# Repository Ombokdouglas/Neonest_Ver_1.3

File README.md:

# Neonest_Ver_1.3
PCB hardware design

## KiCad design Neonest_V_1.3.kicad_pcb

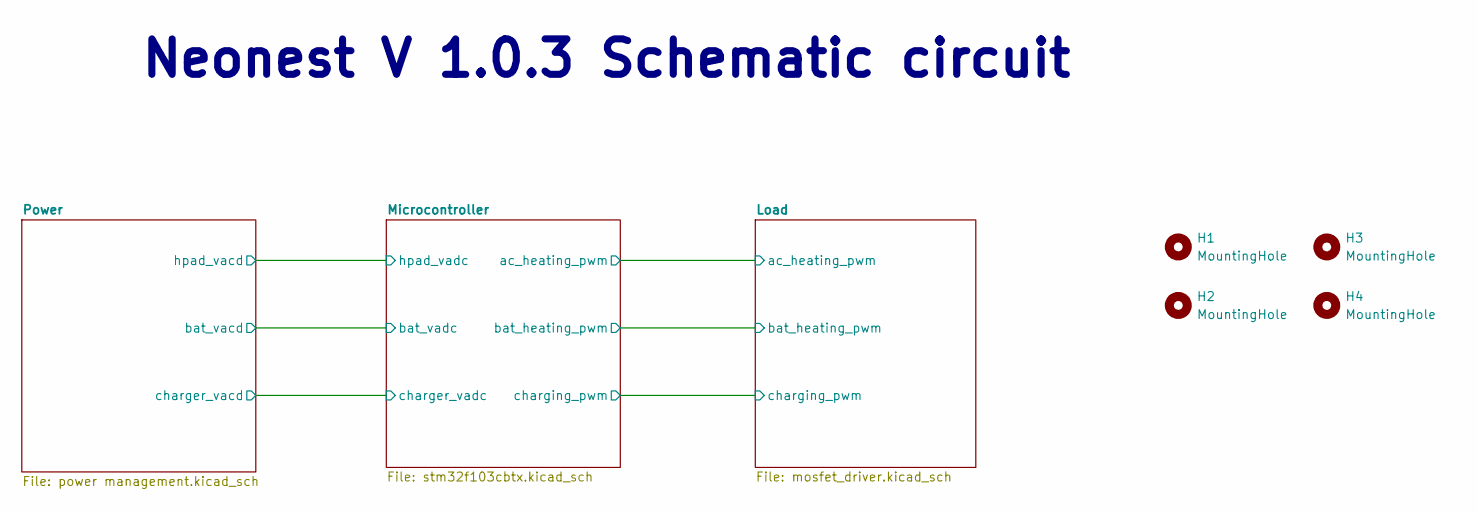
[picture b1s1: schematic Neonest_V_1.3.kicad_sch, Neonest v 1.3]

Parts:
H1, H2, H3, H4: MountingHole; MountingHole_4mm

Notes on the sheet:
Neonest V 1.0.3 Schematic circuit

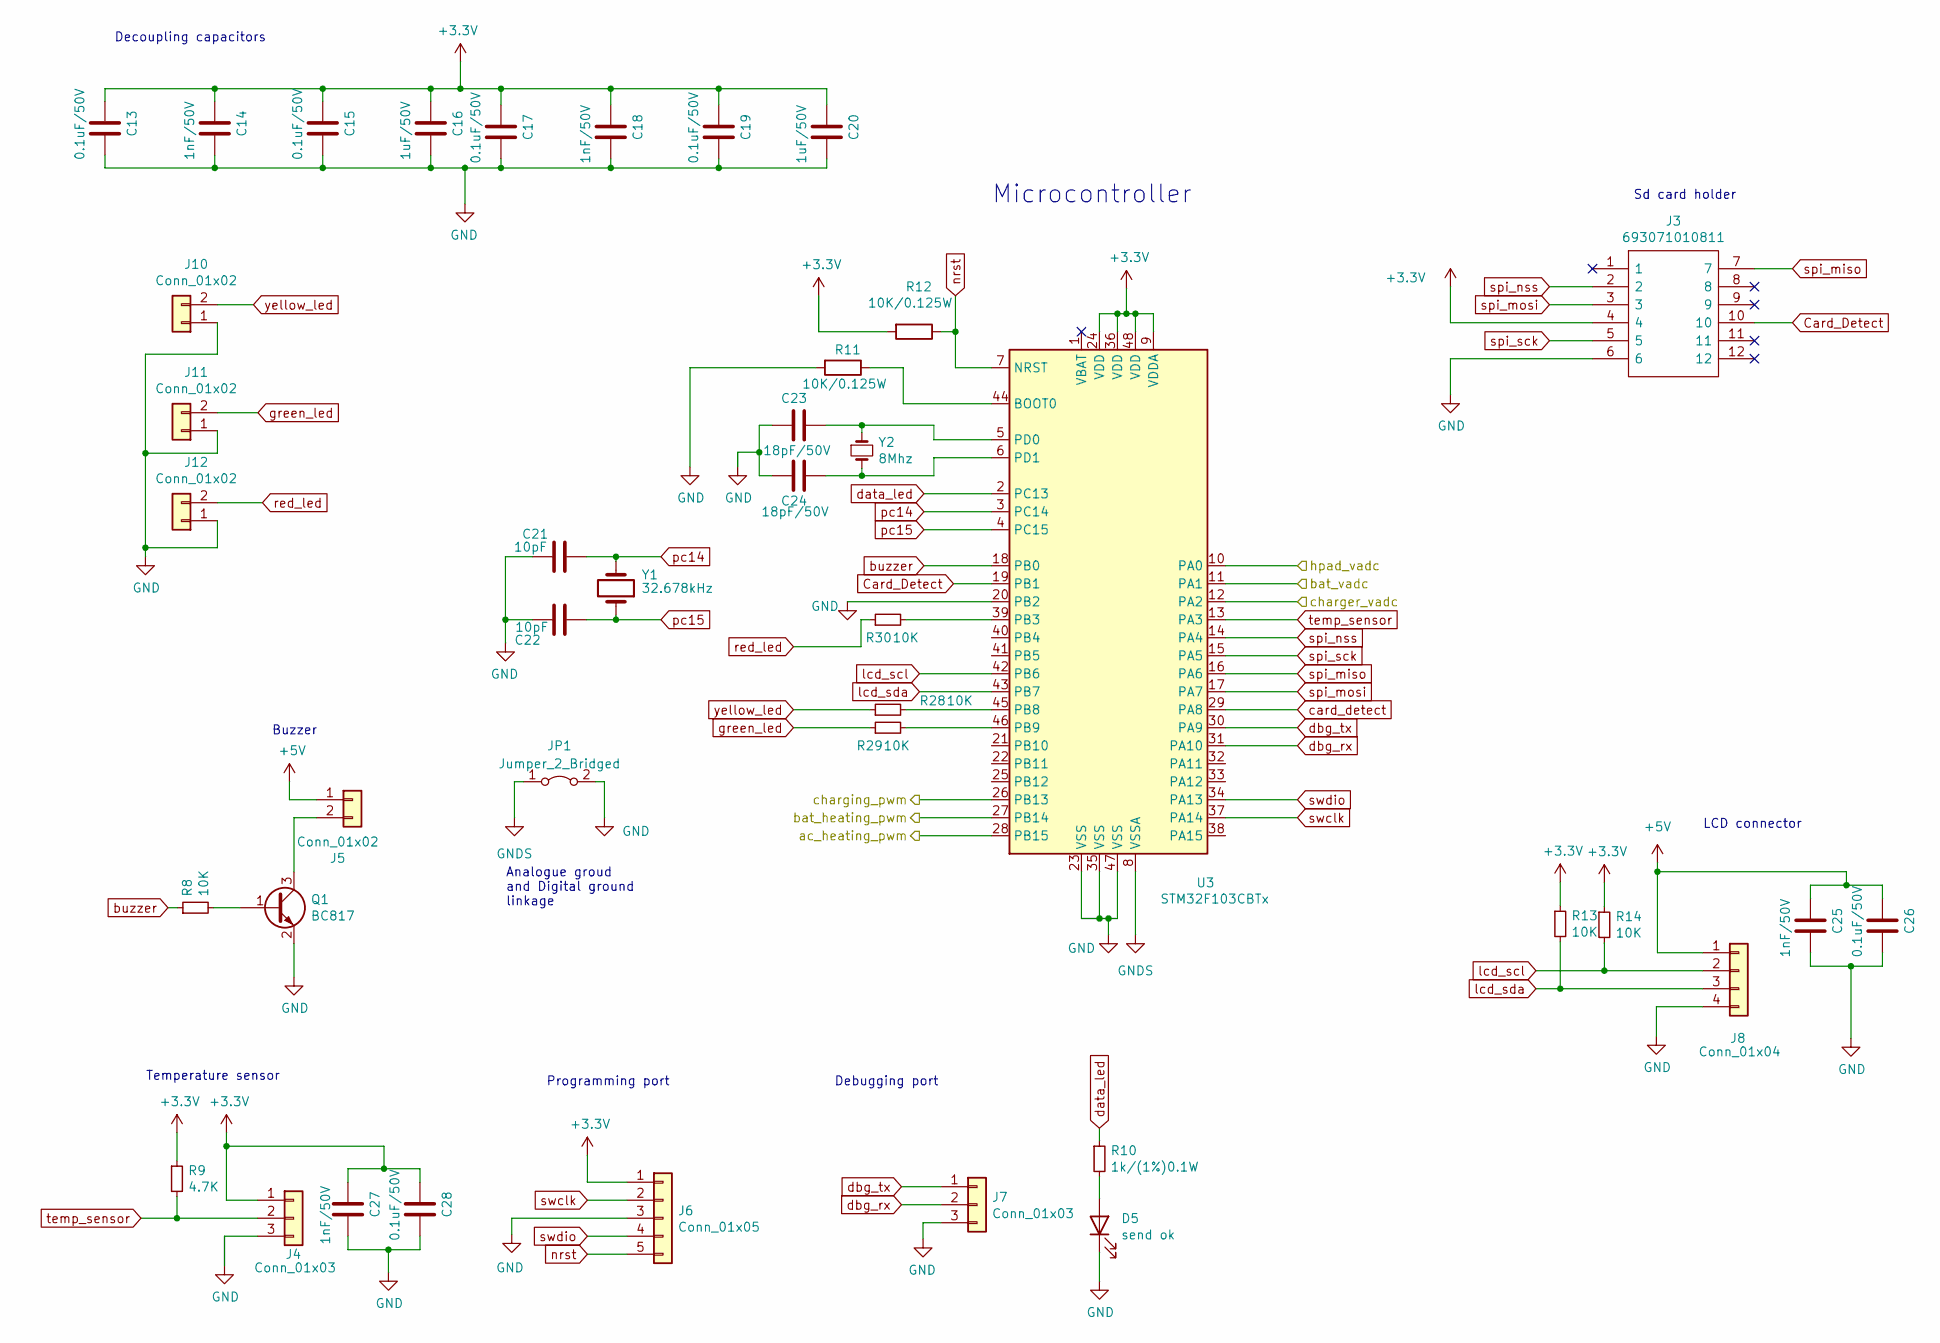
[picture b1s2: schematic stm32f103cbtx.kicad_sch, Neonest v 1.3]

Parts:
C13, C15, C17, C19, C26, C28: 0.1uF/50V; C_0603_1608Metric
C14, C18, C25, C27: 1nF/50V; C_0603_1608Metric
C16, C20: 1uF/50V; C_0603_1608Metric
C21, C22: 10pF; C_0603_1608Metric
C23, C24: 18pF/50V; C_0603_1608Metric
D5: send ok; LED_0603_1608Metric
J3: 693071010811; sd_card; Manufacturer_Part_Number 693071010811; Mouser Part Number 710-693071010811
J4: Conn_01x03; JST_EH_B3B-EH-A_1x03_P2.50mm_Vertical
J5, J10, J11, J12: Conn_01x02; JST_EH_B2B-EH-A_1x02_P2.50mm_Vertical
J6: Conn_01x05; PinHeader_1x05_P2.54mm_Vertical
J7: Conn_01x03; PinHeader_1x03_P2.54mm_Vertical
J8: Conn_01x04; JST_EH_B4B-EH-A_1x04_P2.50mm_Vertical
JP1: Jumper_2_Bridged; SolderJumper-2_P1.3mm_Bridged2Bar_RoundedPad1.0x1.5mm
Q1: BC817; SOT-23
R8, R13, R14, R28, R29, R30: 10K; R_0603_1608Metric
R9: 4.7K; R_0603_1608Metric
R10: 1k/(1%)0.1W; R_0603_1608Metric
R11, R12: 10K/0.125W; R_0603_1608Metric
U3: STM32F103CBTx; LQFP-48_7x7mm_P0.5mm
Y1: 32.678kHz; Crystal_C26-LF_D2.1mm_L6.5mm_Vertical
Y2: 8Mhz; Crystal_HC49-4H_Vertical

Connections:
+3V3: C13.1, C14.1, C15.1, C16.1, C17.1, C18.1, C19.1, C20.1, C27.1, C28.1, J3.4, J4.1, J6.1, R9.1, R12.2, R13.1, R14.1, U3.9 (VDDA), U3.24 (VDD), U3.36 (VDD), U3.48 (VDD); also elsewhere on the board
+5V: C25.1, C26.1, J5.1, J8.1; also elsewhere on the board
/Load/ac_heating_pwm: U3.28 (PB15); also elsewhere on the board
/Load/bat_heating_pwm: U3.27 (PB14); also elsewhere on the board
/Load/charging_pwm: U3.26 (PB13); also elsewhere on the board
/Microcontroller/bat_vadc: U3.11 (PA1); also elsewhere on the board
/Microcontroller/charger_vadc: U3.12 (PA2); also elsewhere on the board
/Microcontroller/hpad_vadc: U3.10 (PA0); also elsewhere on the board
Card_Detect: J3.10, U3.19 (PB1)
GND: C13.2, C14.2, C15.2, C16.2, C17.2, C18.2, C19.2, C20.2, C21.1, C22.1, C23.1, C24.1, C25.2, C26.2, C27.2, C28.2, D5.1 (K), J3.6, J4.3, J6.3, J7.3, J8.4, J10.1, J11.1, J12.1, JP1.2 (B), Q1.2 (E), R11.2, U3.20 (PB2), U3.23 (VSS), U3.35 (VSS), U3.47 (VSS); also elsewhere on the board
GNDS: JP1.1 (A), U3.8 (VSSA); also elsewhere on the board
unnamed: D5.2 (A), R10.2
unnamed: J5.2, Q1.3 (C)
unnamed: Q1.1 (B), R8.2
unnamed: R11.1, U3.44 (BOOT0)
unnamed: R30.2, U3.39 (PB3)
unnamed: R28.2, U3.45 (PB8)
unnamed: R29.2, U3.46 (PB9)
unnamed: C23.2, U3.5 (PD0), Y2.1
unnamed: C24.2, U3.6 (PD1), Y2.2
buzzer: R8.1, U3.18 (PB0)
card_detect: U3.29 (PA8)
data_led: R10.1, U3.2 (PC13)
dbg_rx: J7.2, U3.31 (PA10)
dbg_tx: J7.1, U3.30 (PA9)
green_led: J11.2, R29.1
lcd_scl: J8.2, R14.2, U3.42 (PB6)
lcd_sda: J8.3, R13.2, U3.43 (PB7)
nrst: J6.5, R12.1, U3.7 (NRST)
pc14: C21.2, U3.3 (PC14), Y1.2
pc15: C22.2, U3.4 (PC15), Y1.1
red_led: J12.2, R30.1
spi_miso: J3.7, U3.16 (PA6)
spi_mosi: J3.3, U3.17 (PA7)
spi_nss: J3.2, U3.14 (PA4)
spi_sck: J3.5, U3.15 (PA5)
swclk: J6.2, U3.37 (PA14)
swdio: J6.4, U3.34 (PA13)
temp_sensor: J4.2, R9.2, U3.13 (PA3)
yellow_led: J10.2, R28.1

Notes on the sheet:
Debugging port
Sd card holder
Temperature sensor
Microcontroller
Decoupling capacitors
Analogue groud and Digital ground linkage
LCD connector
Buzzer
Programming port

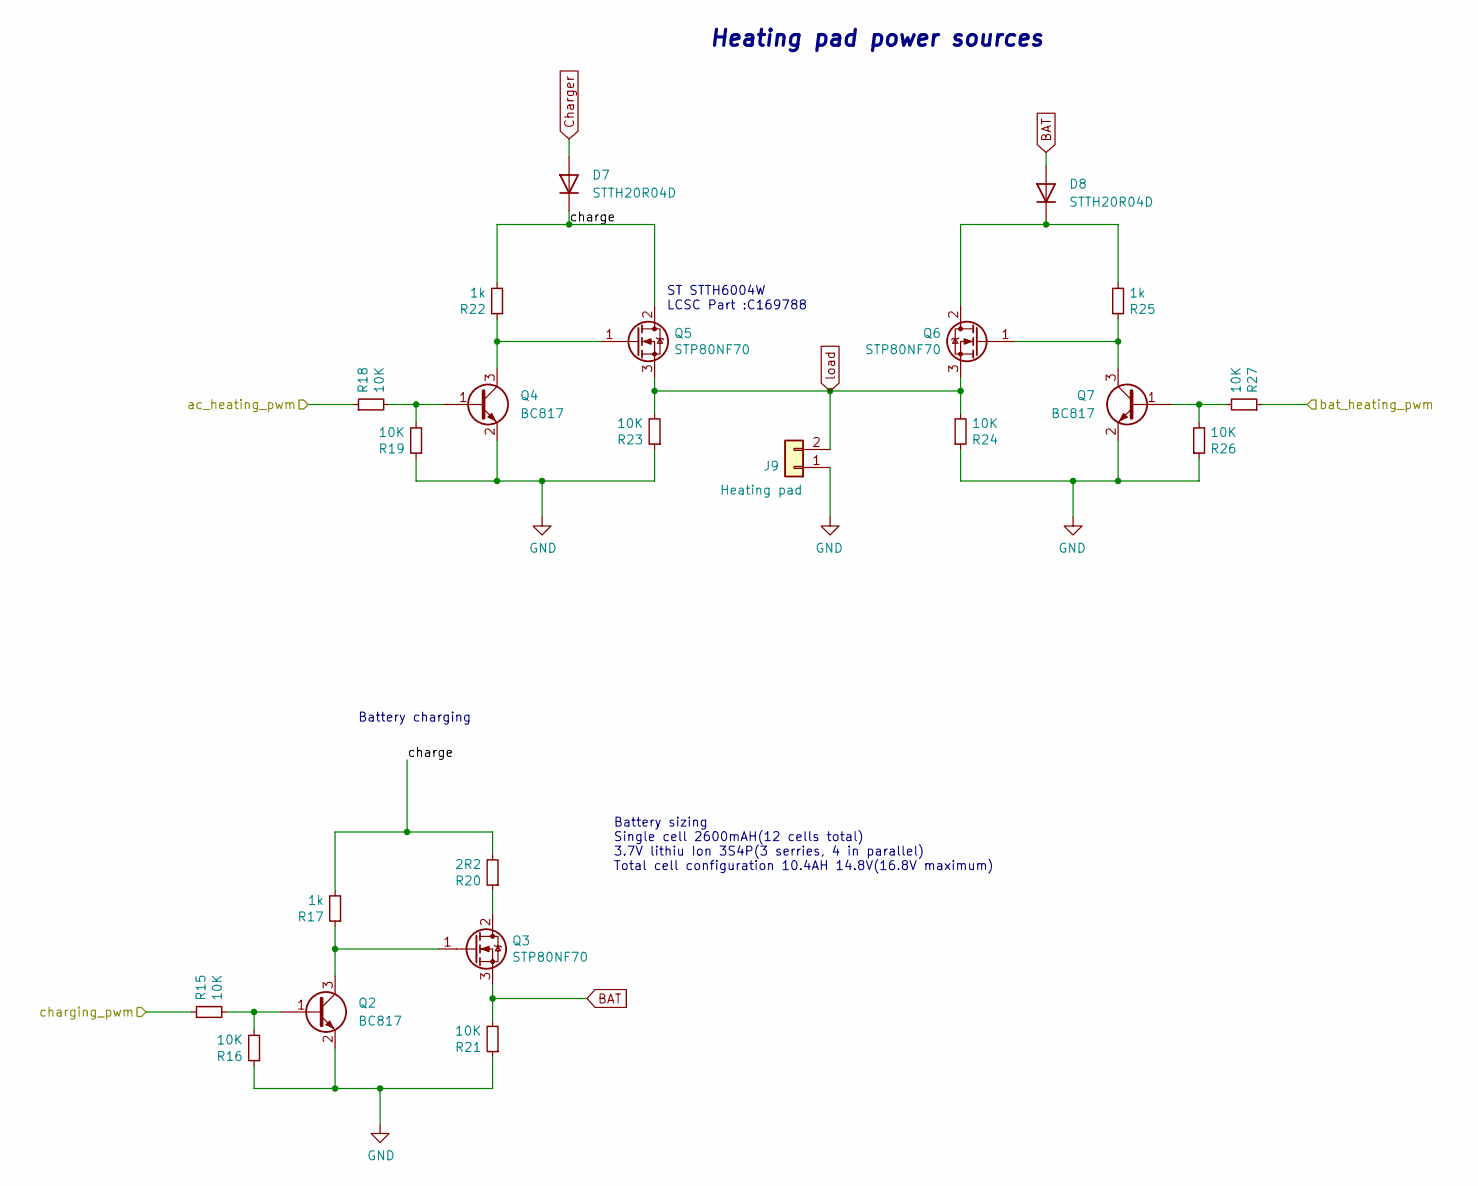
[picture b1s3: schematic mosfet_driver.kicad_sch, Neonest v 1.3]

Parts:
D7, D8: STTH20R04D; TO-220-2_Vertical
J9: Heating pad; TerminalBlock_Dinkle_DT-55-B01X-02_P10.00mm
Q2, Q4, Q7: BC817; SOT-23
Q3, Q5, Q6: STP80NF70; TO-262-3_Vertical
R15, R16, R18, R19, R21, R23, R24, R26, R27: 10K; R_0603_1608Metric
R17, R22, R25: 1k; R_0603_1608Metric
R20: 2R2; R_Axial_DIN0204_L3.6mm_D1.6mm_P7.62mm_Horizontal

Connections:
/Load/ac_heating_pwm: R18.1; also elsewhere on the board
/Load/bat_heating_pwm: R27.1; also elsewhere on the board
/Load/charge: D7.1 (K), Q5.2 (D), R17.2, R20.2, R22.2
/Load/charging_pwm: R15.1; also elsewhere on the board
BAT: D8.2 (A), Q3.3 (S), R21.2; also elsewhere on the board
Charger: D7.2 (A); also elsewhere on the board
GND: J9.1, Q2.2 (E), Q4.2 (E), Q7.2 (E), R16.1, R19.1, R21.1, R23.1, R24.1, R26.1; also elsewhere on the board
unnamed: D8.1 (K), Q6.2 (D), R25.2
unnamed: Q2.1 (B), R15.2, R16.2
unnamed: Q2.3 (C), Q3.1 (G), R17.1
unnamed: Q3.2 (D), R20.1
unnamed: Q4.1 (B), R18.2, R19.2
unnamed: Q4.3 (C), Q5.1 (G), R22.1
unnamed: Q6.1 (G), Q7.3 (C), R25.1
unnamed: Q7.1 (B), R26.2, R27.2
load: J9.2, Q5.3 (S), Q6.3 (S), R23.2, R24.2; also elsewhere on the board

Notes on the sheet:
ST STTH6004W LCSC Part :C169788
Battery charging
Heating pad power sources
Battery sizing Single cell 2600mAH(12 cells total) 3.7V lithiu Ion 3S4P(3 serries, 4 in parallel) Total cell configuration 10.4AH 14.8V(16.8V maximum)

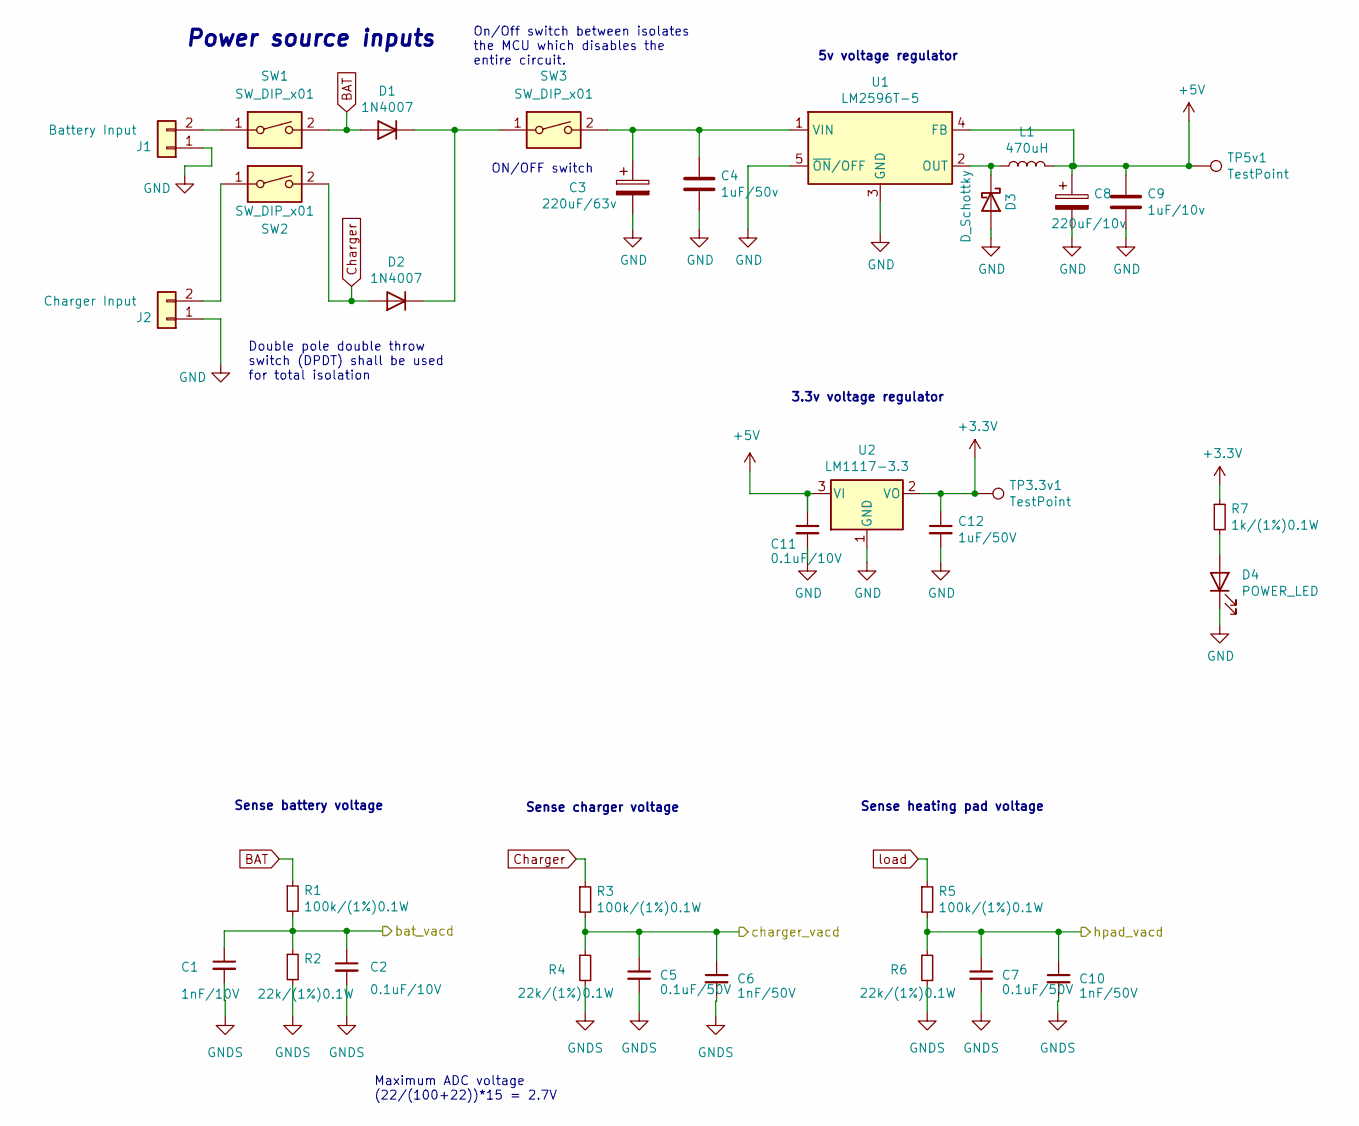
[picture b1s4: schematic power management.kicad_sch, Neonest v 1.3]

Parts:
C1: 1nF/10V; C_0603_1608Metric
C2, C11: 0.1uF/10V; C_0603_1608Metric
C3: 220uF/63v; CP_Elec_8x10
C4: 1uF/50v; C_0603_1608Metric
C5, C7: 0.1uF/50V; C_0603_1608Metric
C6, C10: 1nF/50V; C_0603_1608Metric
C8: 220uF/10v; CP_Elec_8x10
C9: 1uF/10v; C_0603_1608Metric
C12: 1uF/50V; C_0603_1608Metric
D1, D2: 1N4007; D_SMA
D3: D_Schottky; D_SMA
D4: POWER_LED; LED_0603_1608Metric
J1: Battery Input; TerminalBlock_Dinkle_DT-55-B01X-02_P10.00mm
J2: Charger Input; TerminalBlock_Dinkle_DT-55-B01X-02_P10.00mm
L1: 470uH; L_Bourns_SRR1260
R1, R3, R5: 100k/(1%)0.1W; R_0603_1608Metric
R2, R4, R6: 22k/(1%)0.1W; R_0603_1608Metric
R7: 1k/(1%)0.1W; R_0603_1608Metric
SW1, SW2, SW3: SW_DIP_x01; SW_PUSH_1P1T_6x3.5mm_H5.0_APEM_MJTP1250
TP3.3v1, TP5v1: TestPoint; TestPoint_Pad_D1.0mm
U1: LM2596T-5; TO-263-5_TabPin3
U2: LM1117-3.3; SOT-223-3_TabPin2

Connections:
+3V3: C12.1, R7.1, TP3.3v1.1, U2.2 (VO); also elsewhere on the board
+5V: C8.1, C9.1, C11.1, L1.2, TP5v1.1, U1.4 (FB), U2.3 (VI); also elsewhere on the board
/Microcontroller/bat_vadc: C1.1, C2.1, R1.2, R2.1; also elsewhere on the board
/Microcontroller/charger_vadc: C5.1, C6.1, R3.2, R4.1; also elsewhere on the board
/Microcontroller/hpad_vadc: C7.1, C10.1, R5.2, R6.1; also elsewhere on the board
BAT: D1.2 (A), R1.1, SW1.2; also elsewhere on the board
Charger: D2.2 (A), R3.1, SW2.2; also elsewhere on the board
GND: C3.2, C4.2, C8.2, C9.2, C11.2, C12.2, D3.2 (A), D4.1 (K), J1.1, J2.1, U1.3 (GND), U1.5 (~ON/OFF), U2.1 (GND); also elsewhere on the board
GNDS: C1.2, C2.2, C5.2, C6.2, C7.2, C10.2, R2.2, R4.2, R6.2; also elsewhere on the board
unnamed: D1.1 (K), D2.1 (K), SW3.1
unnamed: D3.1 (K), L1.1, U1.2 (OUT)
unnamed: D4.2 (A), R7.2
unnamed: J1.2, SW1.1
unnamed: J2.2, SW2.1
unnamed: C3.1, C4.1, SW3.2, U1.1 (VIN)
load: R5.1; also elsewhere on the board

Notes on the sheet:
Sense heating pad voltage
On/Off switch between isolates the MCU which disables the entire circuit.
Double pole double throw switch (DPDT) shall be used for total isolation
3.3v voltage regulator
Maximum ADC voltage (22/(100+22))*15 = 2.7V
5v voltage regulator
Sense charger voltage
ON/OFF switch
Power source inputs
Sense battery voltage

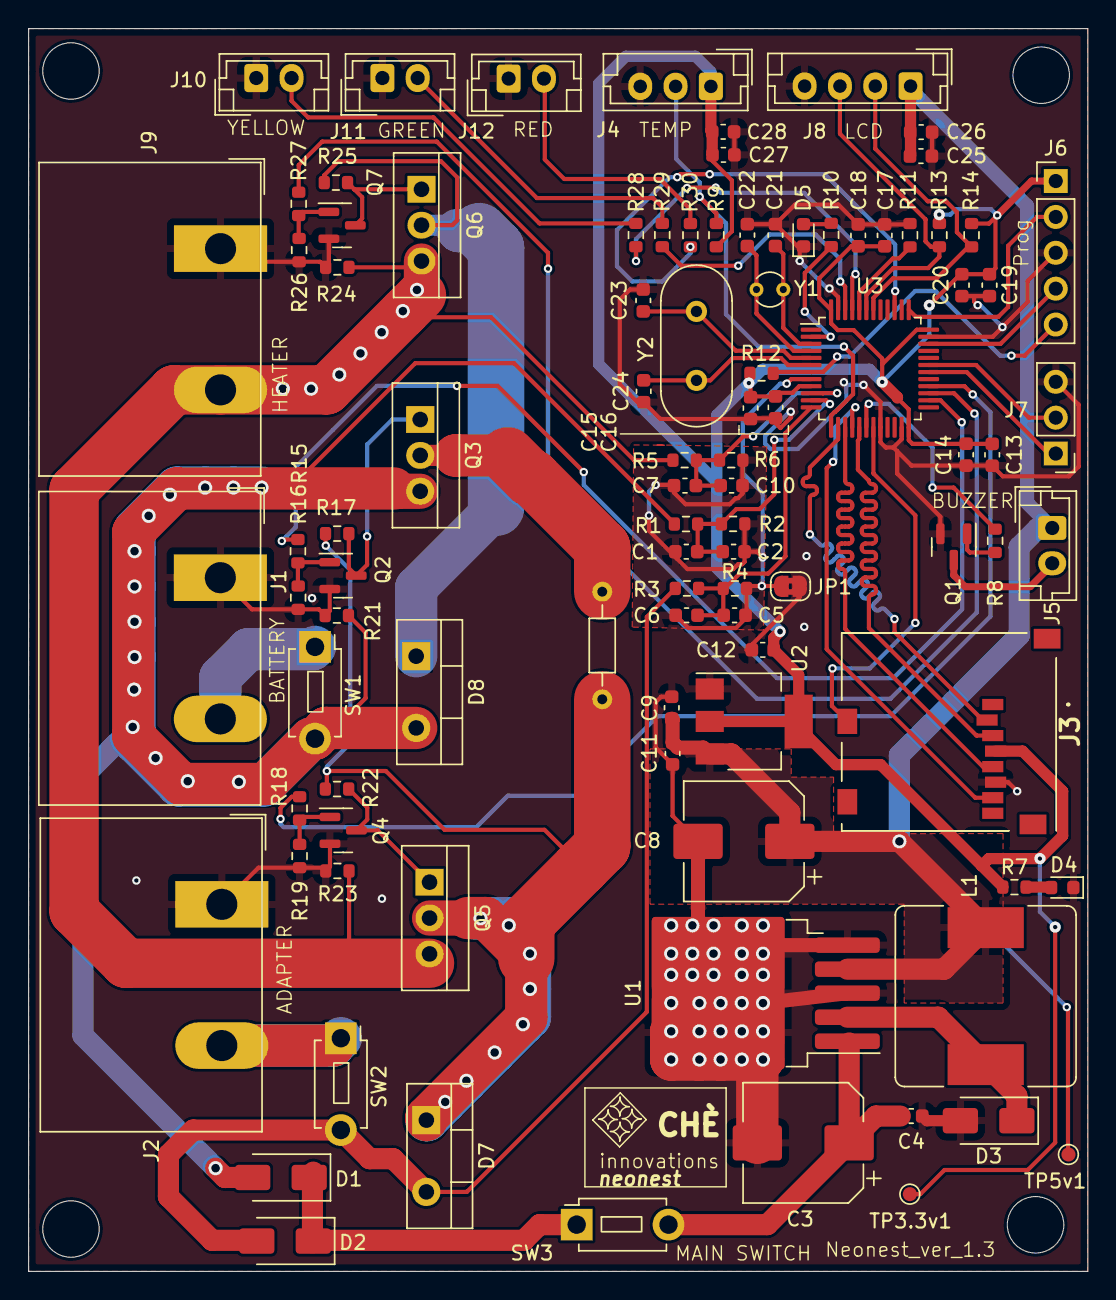
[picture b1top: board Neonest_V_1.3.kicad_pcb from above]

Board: 2 copper layers, 75.0 x 88.0 mm, 100 parts (0 on the bottom side), 57 nets.

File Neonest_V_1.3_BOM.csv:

"Id";"Designator";"Footprint";"Quantity";"Designation";"Supplier and ref";
1;"U3";"LQFP-48_7x7mm_P0.5mm";1;"STM32F103CBTx";;;
2;"R1,R3,R5";"R_0603_1608Metric";3;"180k/(1%)0.1W";;;
3;"C8";"CP_Elec_8x10";1;"220uF/10v";;;
4;"C27,C14,C6,C10,C18,C25";"C_0603_1608Metric";6;"1nF/50V";;;
5;"TP5v1,TP3.3v1";"TestPoint_Pad_D1.0mm";2;"TestPoint";;;
6;"C3";"CP_Elec_8x10";1;"220uF/63v";;;
7;"D3";"D_SMA";1;"D_Schottky";;;
8;"D4";"LED_0603_1608Metric";1;"POWER_LED";;;
9;"R16,R19,R27,R29,R8,R18,R15,R14,R24,R30,R28,R21,R26,R23,R13";"R_0603_1608Metric";15;"10K";;;
10;"C17,C5,C28,C13,C19,C7,C26,C15";"C_0603_1608Metric";8;"0.1uF/50V";;;
11;"R10,R7";"R_0603_1608Metric";2;"1k/(1%)0.1W";;;
12;"Q4,Q2,Q7,Q1";"SOT-23";4;"BC817";;;
13;"Q6,Q3,Q5";"TO-262-3_Vertical";3;"STB33N65M2";;;
14;"H4,H3,H1,H2";"MountingHole_4mm";4;"MountingHole";;;
15;"U1";"TO-263-5_TabPin3";1;"LM2596T-5";;;
16;"R11,R12";"R_0603_1608Metric";2;"10K/0.125W";;;
17;"C22,C21";"C_0603_1608Metric";2;"10pF";;;
18;"R22,R17,R25";"R_0603_1608Metric";3;"1k";;;
19;"ADAPTER";"TerminalBlock_Dinkle_DT-55-B01X-02_P10.00mm";1;"Charger Input";;;
20;"GREEN,YELLOW,RED,J5";"JST_EH_B2B-EH-A_1x02_P2.50mm_Vertical";4;"Conn_01x02";;;
21;"R6,R4";"R_0603_1608Metric";2;"5.1k/(1%)0.1W";;;
22;"J6";"PinHeader_1x05_P2.54mm_Vertical";1;"Conn_01x05";;;
23;"R20";"R_0603_1608Metric";1;"0R";;;
24;"HEATER";"TerminalBlock_Dinkle_DT-55-B01X-02_P10.00mm";1;"Heating pad";;;
25;"LCD";"JST_EH_B4B-EH-A_1x04_P2.50mm_Vertical";1;"Conn_01x04";;;
26;"REF**";"neonest_logo";1;"neonest_logo";;;
27;"C11,C2";"C_0603_1608Metric";2;"0.1uF/10V";;;
28;"D1,D2";"D_SMA";2;"1N4007";;;
29;"Y1";"Crystal_C26-LF_D2.1mm_L6.5mm_Vertical";1;"32.678kHz";;;
30;"J3";"sd_card";1;"693071010811";;;
31;"R2";"R_0603_1608Metric";1;"10k/(1%)0.1W";;;
32;"C4";"C_0603_1608Metric";1;"1uF/50v";;;
33;"D5";"LED_0603_1608Metric";1;"send ok";;;
34;"C12,C20,C16";"C_0603_1608Metric";3;"1uF/50V";;;
35;"D8,D7";"TO-220-2_Vertical";2;"STTH2002D";;;
36;"Y2";"Crystal_HC49-4H_Vertical";1;"8Mhz";;;
37;"C23,C24";"C_0603_1608Metric";2;"18pF/50V";;;
38;"TP2,TP1";"TestPoint_Pad_D2.5mm";2;"TestPoint";;;
39;"C1";"C_0603_1608Metric";1;"1nF/10V";;;
40;"TEMP";"JST_EH_B3B-EH-A_1x03_P2.50mm_Vertical";1;"Conn_01x03";;;
41;"U2";"SOT-223-3_TabPin2";1;"LM1117-3.3";;;
42;"BATTERY";"TerminalBlock_Dinkle_DT-55-B01X-02_P10.00mm";1;"Battery Input";;;
43;"L1";"L_Bourns_SRR1260";1;"470uH";;;
44;"J7";"PinHeader_1x03_P2.54mm_Vertical";1;"Conn_01x03";;;
45;"C9";"C_0603_1608Metric";1;"1uF/10v";;;
46;"R9";"R_0603_1608Metric";1;"4.7K";;;

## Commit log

2025-08-04 updated silkscreen information
2025-08-08 Formatted schematic and Increased power tracks
2025-08-08 Battery sizing
2025-08-08 Few final amendments on sizing and BOM editing
2025-08-15 Minor changes, generated gerber files and submitted
